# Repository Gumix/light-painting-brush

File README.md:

View this project on [CADLAB.io](https://cadlab.io/node/803). 

# light-painting-brush

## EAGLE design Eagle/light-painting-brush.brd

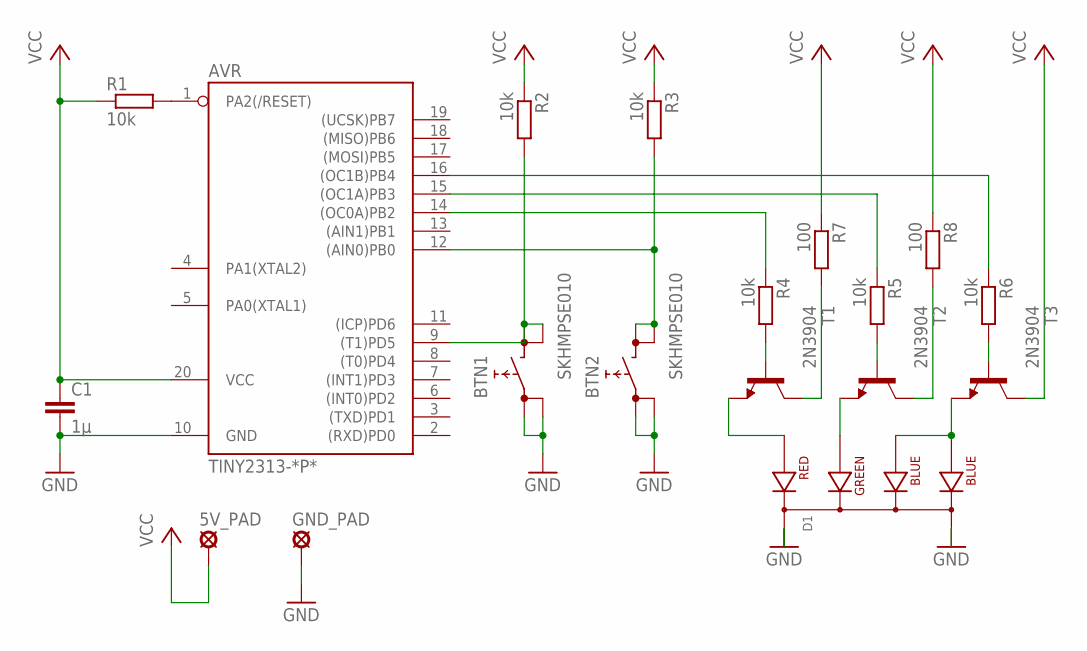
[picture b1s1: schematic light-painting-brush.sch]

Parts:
5V_PAD: LSP10
AVR: TINY2313-*P*; DIL20
BTN1, BTN2: SKHMPSE010; SKHMPXE010
C1: 1μ; C1206
D1: LED-RGB-CC-THRUDIFFUSE; LED-RGB-THRU
GND_PAD: LSP10
R1, R2, R3, R4, R5, R6: 10k; R1206
R7, R8: 100; R1206
T1, T2, T3: 2N3904; TO92

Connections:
BLUE: D1.BLUE1, D1.BLUE2, T3.3 (E)
BLUE0: AVR.16 ((OC1B)PB4), R6.1
BLUE1: R6.2, T3.2 (B)
GND: AVR.10 (GND), BTN1.1 (1.1), BTN1.2 (1.2), BTN2.1 (1.1), BTN2.2 (1.2), C1.2, D1.CATHODE1, D1.CATHODE2, GND_PAD.MP
GREEN: D1.GREEN, T2.3 (E)
GREEN0: AVR.15 ((OC1A)PB3), R5.1
GREEN1: R5.2, T2.2 (B)
GREEN2: R8.2, T2.1 (C)
unnamed: AVR.1 (PA2(/RESET)), R1.2
unnamed: AVR.9 ((T1)PD5), BTN1.3 (2.1), BTN1.4 (2.2), R2.2
unnamed: AVR.12 ((AIN0)PB0), BTN2.3 (2.1), BTN2.4 (2.2), R3.2
RED: D1.RED, T1.3 (E)
RED0: AVR.14 ((OC0A)PB2), R4.1
RED1: R4.2, T1.2 (B)
RED2: R7.2, T1.1 (C)
VCC: 5V_PAD.MP, AVR.20 (VCC), C1.1, R1.1, R2.1, R3.1, R7.1, R8.1, T3.1 (C)

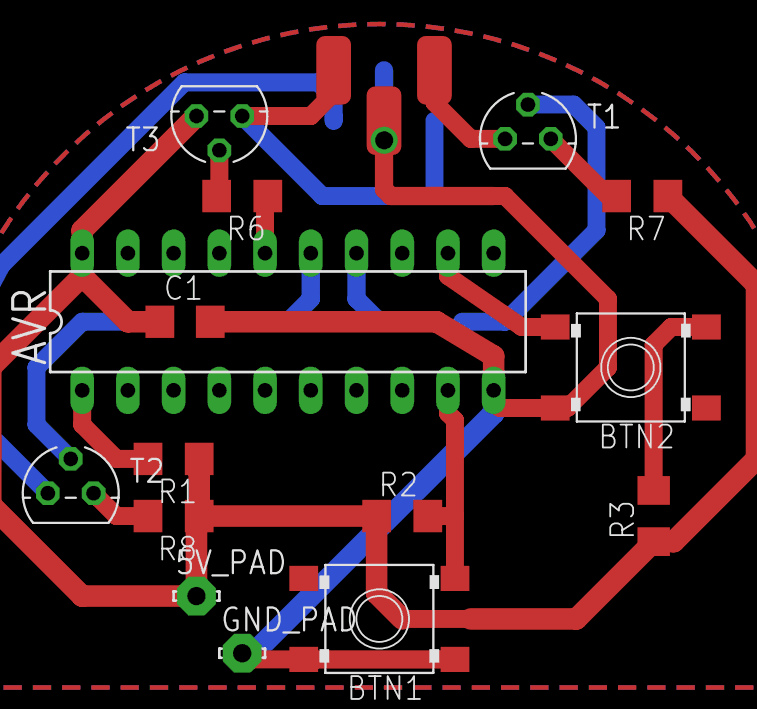
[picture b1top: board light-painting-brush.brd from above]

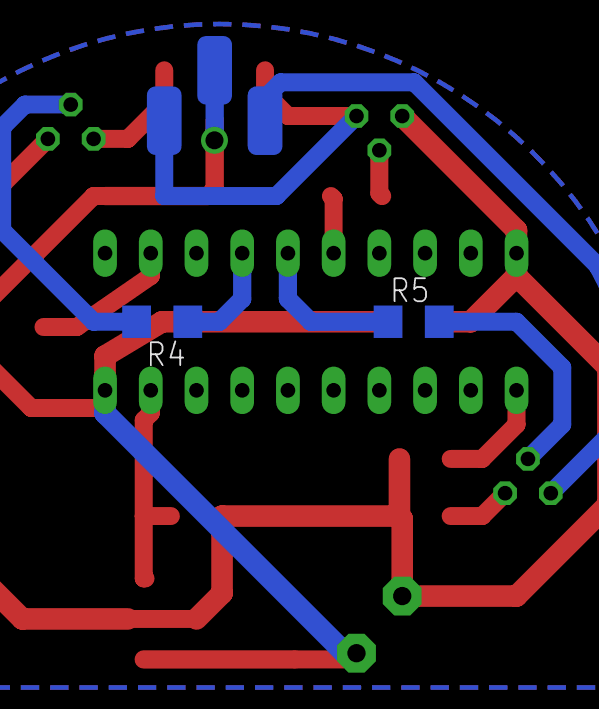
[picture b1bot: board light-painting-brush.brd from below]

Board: 2 copper layers, 18 parts (2 on the bottom side), 16 nets.

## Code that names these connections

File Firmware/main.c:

#include <stddef.h>
#include <stdbool.h>
#include <avr/io.h>
#include <avr/sleep.h>
#include <avr/interrupt.h>

#define RED   OCR0A	// PB2
#define GREEN OCR1A	// PB3
#define BLUE  OCR1B	// PB4
#define BTN1  PD5	// Turn LEDs on
#define BTN2  PB0	// Switch colors

#define BIT_GET(x, b)	((x) & _BV(b))
#define BIT_SET(x, y)	((x) |= _BV(y))
#define BIT_CLR(x, y)	((x) &= ~_BV(y))
#define BTN1_PRESSED	(!BIT_GET(PIND, BTN1))
#define BTN2_PRESSED	(!BIT_GET(PINB, BTN2))

typedef struct
{
	uint8_t r, g, b;
} color_t;

static const color_t palette[] =
{
	{ 255, 0,   0   },	// Red
	{ 255, 128, 0   },	// Orange
	{ 255, 255, 0   },	// Yellow
	{ 0,   255, 0   },	// Green
	{ 0,   255, 255 },	// Cyan
	{ 0,   128, 255 },	// Azure
	{ 0,   0,   255 },	// Blue
	{ 128, 0,   255 },	// Violet
	{ 255, 0,   255 },	// Magenta
	{ 255, 0,   128 }	// Rose
};

#define NUM_COLORS	(sizeof(palette) / sizeof(palette[0]))

static void switch_color()
{
	static size_t color_idx;

	color_t c = palette[color_idx];
	RED   = c.r;
	GREEN = c.g;
	BLUE  = c.b;

	color_idx = (color_idx + 1) % NUM_COLORS;
}

static void switch_leds(bool on)
{
	if (on)
	{
		// Enable PWMs
		BIT_SET(TCCR0A, COM0A1);
		BIT_SET(TCCR1A, COM1A1);
		BIT_SET(TCCR1A, COM1B1);
	}
	else
	{
		// Disable PWMs
		BIT_CLR(TCCR0A, COM0A1);
		BIT_CLR(TCCR1A, COM1A1);
		BIT_CLR(TCCR1A, COM1B1);

		// Zero out output values
		PORTB = 0;
	}
}

static void init(void)
{
	// PB0 - Input, PB2-PB4 - Output
	DDRB  = 0b00011100;

	// Timer/Counter0: Fast PWM mode, Top = 0xFF, No prescaling
	TCCR0A = _BV(WGM01) | _BV(WGM00);
	TCCR0B = _BV(CS00);

	// Timer/Counter1: Fast PWM mode (8 bit), Top = 0xFF, No prescaling
	TCCR1A = _BV(WGM12) | _BV(WGM10);
	TCCR1B = _BV(CS10);

	TIFR  = _BV(TOV0);	// Clear Timer/Counter0 Overflow Flag
	TIMSK = _BV(TOIE0);	// Timer/Counter0 Overflow Interrupt Enable

	switch_color();
	switch_leds(false);

	sei();	// Enable interrupts
}

// Timer/Counter0 Overflow Interrupt (2 kHz)
ISR(TIMER0_OVF_vect)
{
	// Based on "A Guide to Debouncing" by Jack G. Ganssle
	static uint16_t btn2_state;
	btn2_state = (btn2_state << 1) | !BTN2_PRESSED | 0xe000;
	if (btn2_state == 0xf000)
		switch_color();

	switch_leds(BTN1_PRESSED);
}

int main()
{
	init();

	while (true)
		sleep_mode();
}

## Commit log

2018-03-29 Backlink to CADLAB.io has been added.
2020-10-23 Add Autodesk EAGLE project
2020-10-23 Remove TPS61070 boost converter
    Previous version of the board is saved in the "tps61070" branch.
2020-10-27 Redesign the PCB assuming 4V input
2020-10-29 Move C1 closer to VCC and GND pins of AVR
2020-11-22 Update values assuming 5V input
2021-01-17 Add initial firmware
2021-10-24 Use 3 PWM channels for setting RGB intensities
2021-10-24 Add a palette with 10 colors
2021-10-24 Process buttons in the Timer/Counter Overflow Interrupt
    Button 1 - Turn LEDs on
    Button 2 - Switch colors
2021-10-24 Implment contact debouncing
    Based on "A Guide to Debouncing" by Jack G. Ganssle:
    http://ohm.bu.edu/~pbohn/__Engineering_Reference/debouncing.pdf
2021-10-24 Add HEX file with the firmware
